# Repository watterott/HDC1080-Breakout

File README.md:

# HDC1080-Breakout
Breakout with TI HDC1080 Digital Humidity and Temperature Sensor.

* [TI HDC1080](https://www.ti.com/product/hdc1080) Digital Humidity and Temperature Sensor
* Relative Humidity (RH) operating range: 0% to 100%
* Relative Humidity accuracy: +/-2%
* Temperature accuracy: +/-0.2°C
* TWI/I2C Interface (address: 0x40)
* 3.3V - 5V Power Supply and Logic Level
* Open-Source and released under the [Creative Commons Attribution Share-Alike License](https://creativecommons.org/licenses/by-sa/4.0/).
* **[Documentation on learn.watterott.com](https://learn.watterott.com)**

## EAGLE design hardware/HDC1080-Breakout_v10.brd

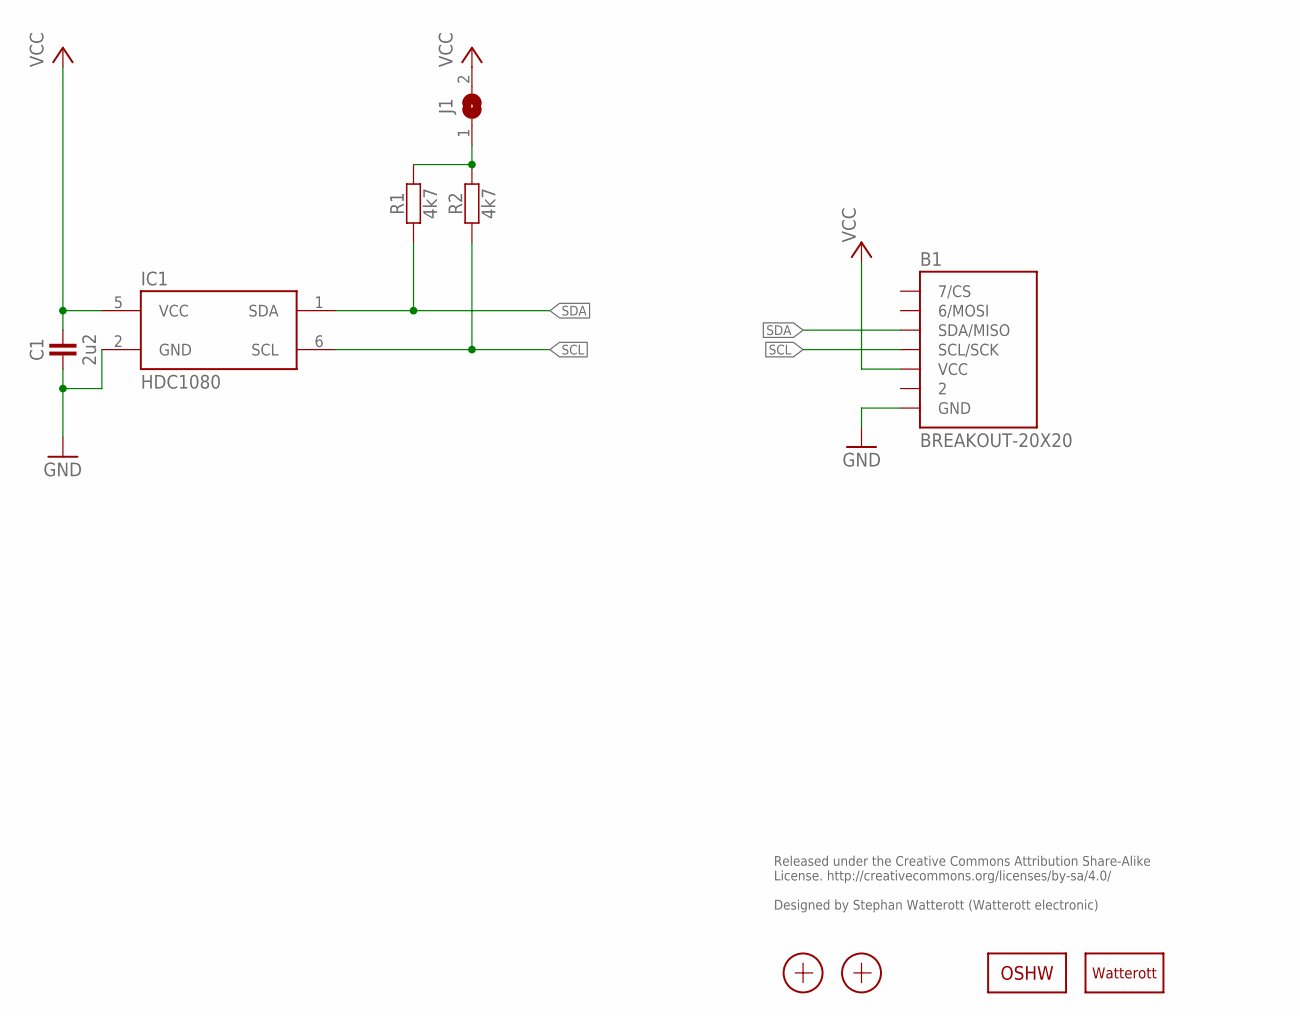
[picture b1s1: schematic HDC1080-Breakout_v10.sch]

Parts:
B1: BREAKOUT-20X20
C1: 2u2; R0402
IC1: HDC1080; WSON6
J1: JUMPER2-0603
LOGO2: OSHW_LOGOX0070; OSHW_6X70
LOGO3: LOGO-S_PLACE_M; SPARK_TPLACE_M
R1, R2: 4k7; R0402
X1, X2: PASSER-07; PASSER_07MM

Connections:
GND: B1.GND, C1.1, IC1.2 (GND)
unnamed: J1.1, R1.2, R2.2
SCL: B1.SCL/SCK, IC1.6 (SCL), R2.1
SDA: B1.SDA/MISO, IC1.1 (SDA), R1.1
VCC: B1.VCC, C1.2, IC1.5 (VCC), J1.2

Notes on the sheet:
Released under the Creative Commons Attribution Share-Alike License. http://creativecommons.org/licenses/by-sa/4.0/ Designed by Stephan Watterott (Watterott electronic)

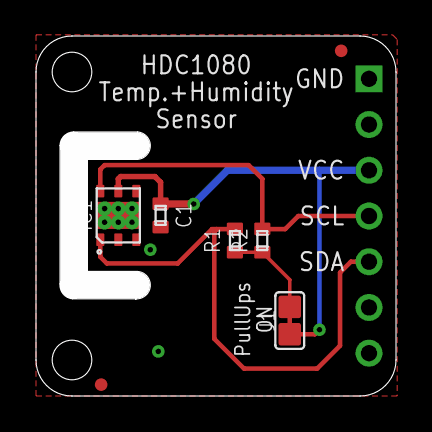
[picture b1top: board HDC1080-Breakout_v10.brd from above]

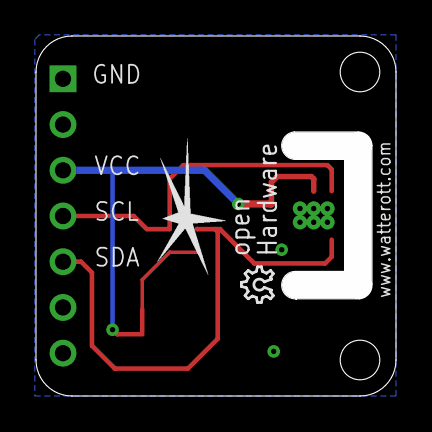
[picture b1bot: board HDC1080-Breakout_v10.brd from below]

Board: 2 copper layers, 18.5 x 18.5 mm, 10 parts (2 on the bottom side), 5 nets.
